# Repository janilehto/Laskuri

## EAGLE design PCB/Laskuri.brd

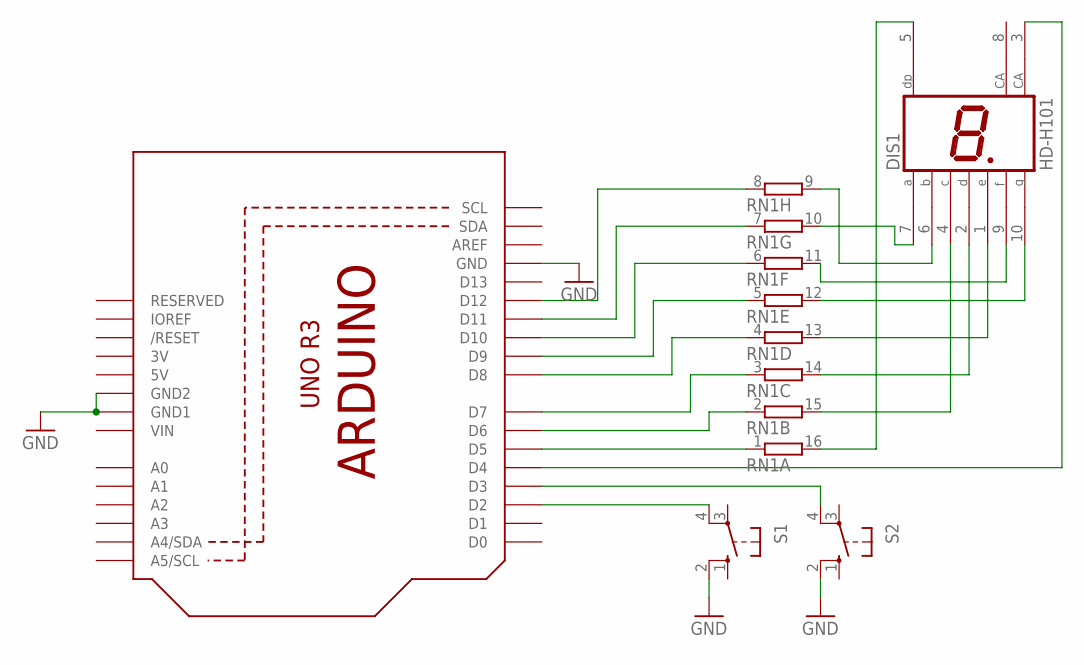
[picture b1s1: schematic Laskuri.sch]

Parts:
DIS1: HD-H101; HDSP-M
RN1: 8R-N; DIL16
S1, S2: 10-XX; B3F-10XX
U1: ARDUINOR3-DIMENSION; ARDUINOR3

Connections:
3V: U1.3V
5V: U1.5V
GND: S1.2 (S1), S2.2 (S1), U1.GND, U1.GND1, U1.GND2
unnamed: RN1.8 (1), U1.D12
unnamed: RN1.7 (1), U1.D11
unnamed: RN1.6 (1), U1.D10
unnamed: RN1.5 (1), U1.D9
unnamed: RN1.4 (1), U1.D8
unnamed: RN1.3 (1), U1.D7
unnamed: RN1.2 (1), U1.D6
unnamed: RN1.1, U1.D5
unnamed: DIS1.1 (E), RN1.13 (2)
unnamed: S1.4 (P1), U1.D2
unnamed: S2.4 (P1), U1.D3
unnamed: DIS1.2 (D), RN1.14 (2)
unnamed: DIS1.4 (C), RN1.15 (2)
unnamed: DIS1.5 (DP), RN1.16 (2)
unnamed: DIS1.10 (G), RN1.12 (2)
unnamed: DIS1.9 (F), RN1.11 (2)
unnamed: DIS1.7 (A), RN1.10 (2)
unnamed: DIS1.6 (B), RN1.9 (2)
unnamed: DIS1.3 (CA), U1.D4
VIN: U1.VIN

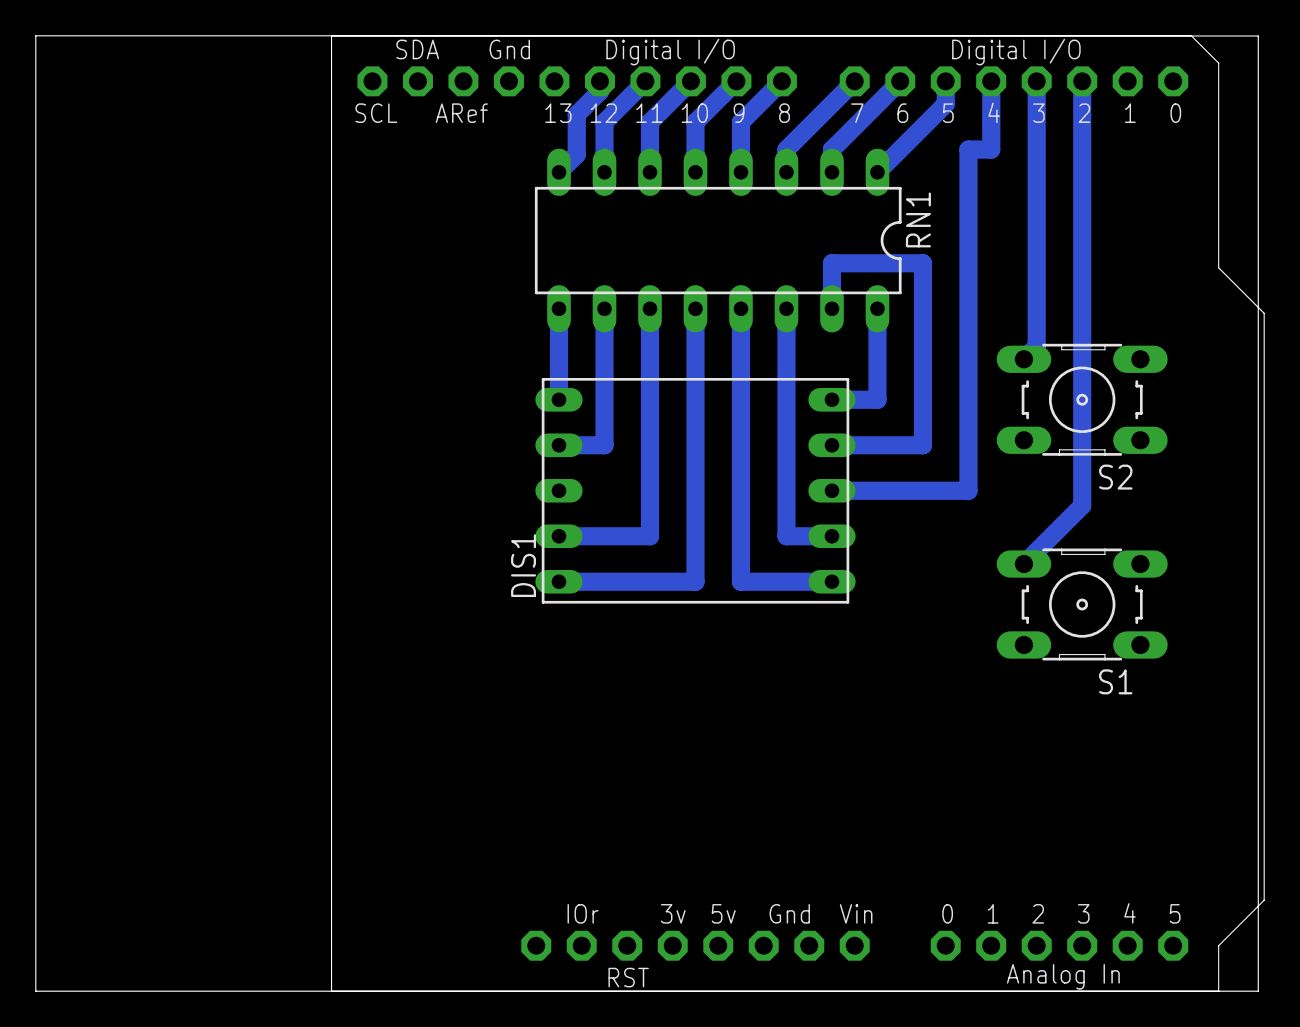
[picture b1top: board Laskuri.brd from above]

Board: 2 copper layers, 68.6 x 53.3 mm, 5 parts (0 on the bottom side), 20 nets.

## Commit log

2019-12-17 Initial import
2019-12-18 Kirjoitusvirheiden korjaus
2020-01-07 Added schemtic PDF
